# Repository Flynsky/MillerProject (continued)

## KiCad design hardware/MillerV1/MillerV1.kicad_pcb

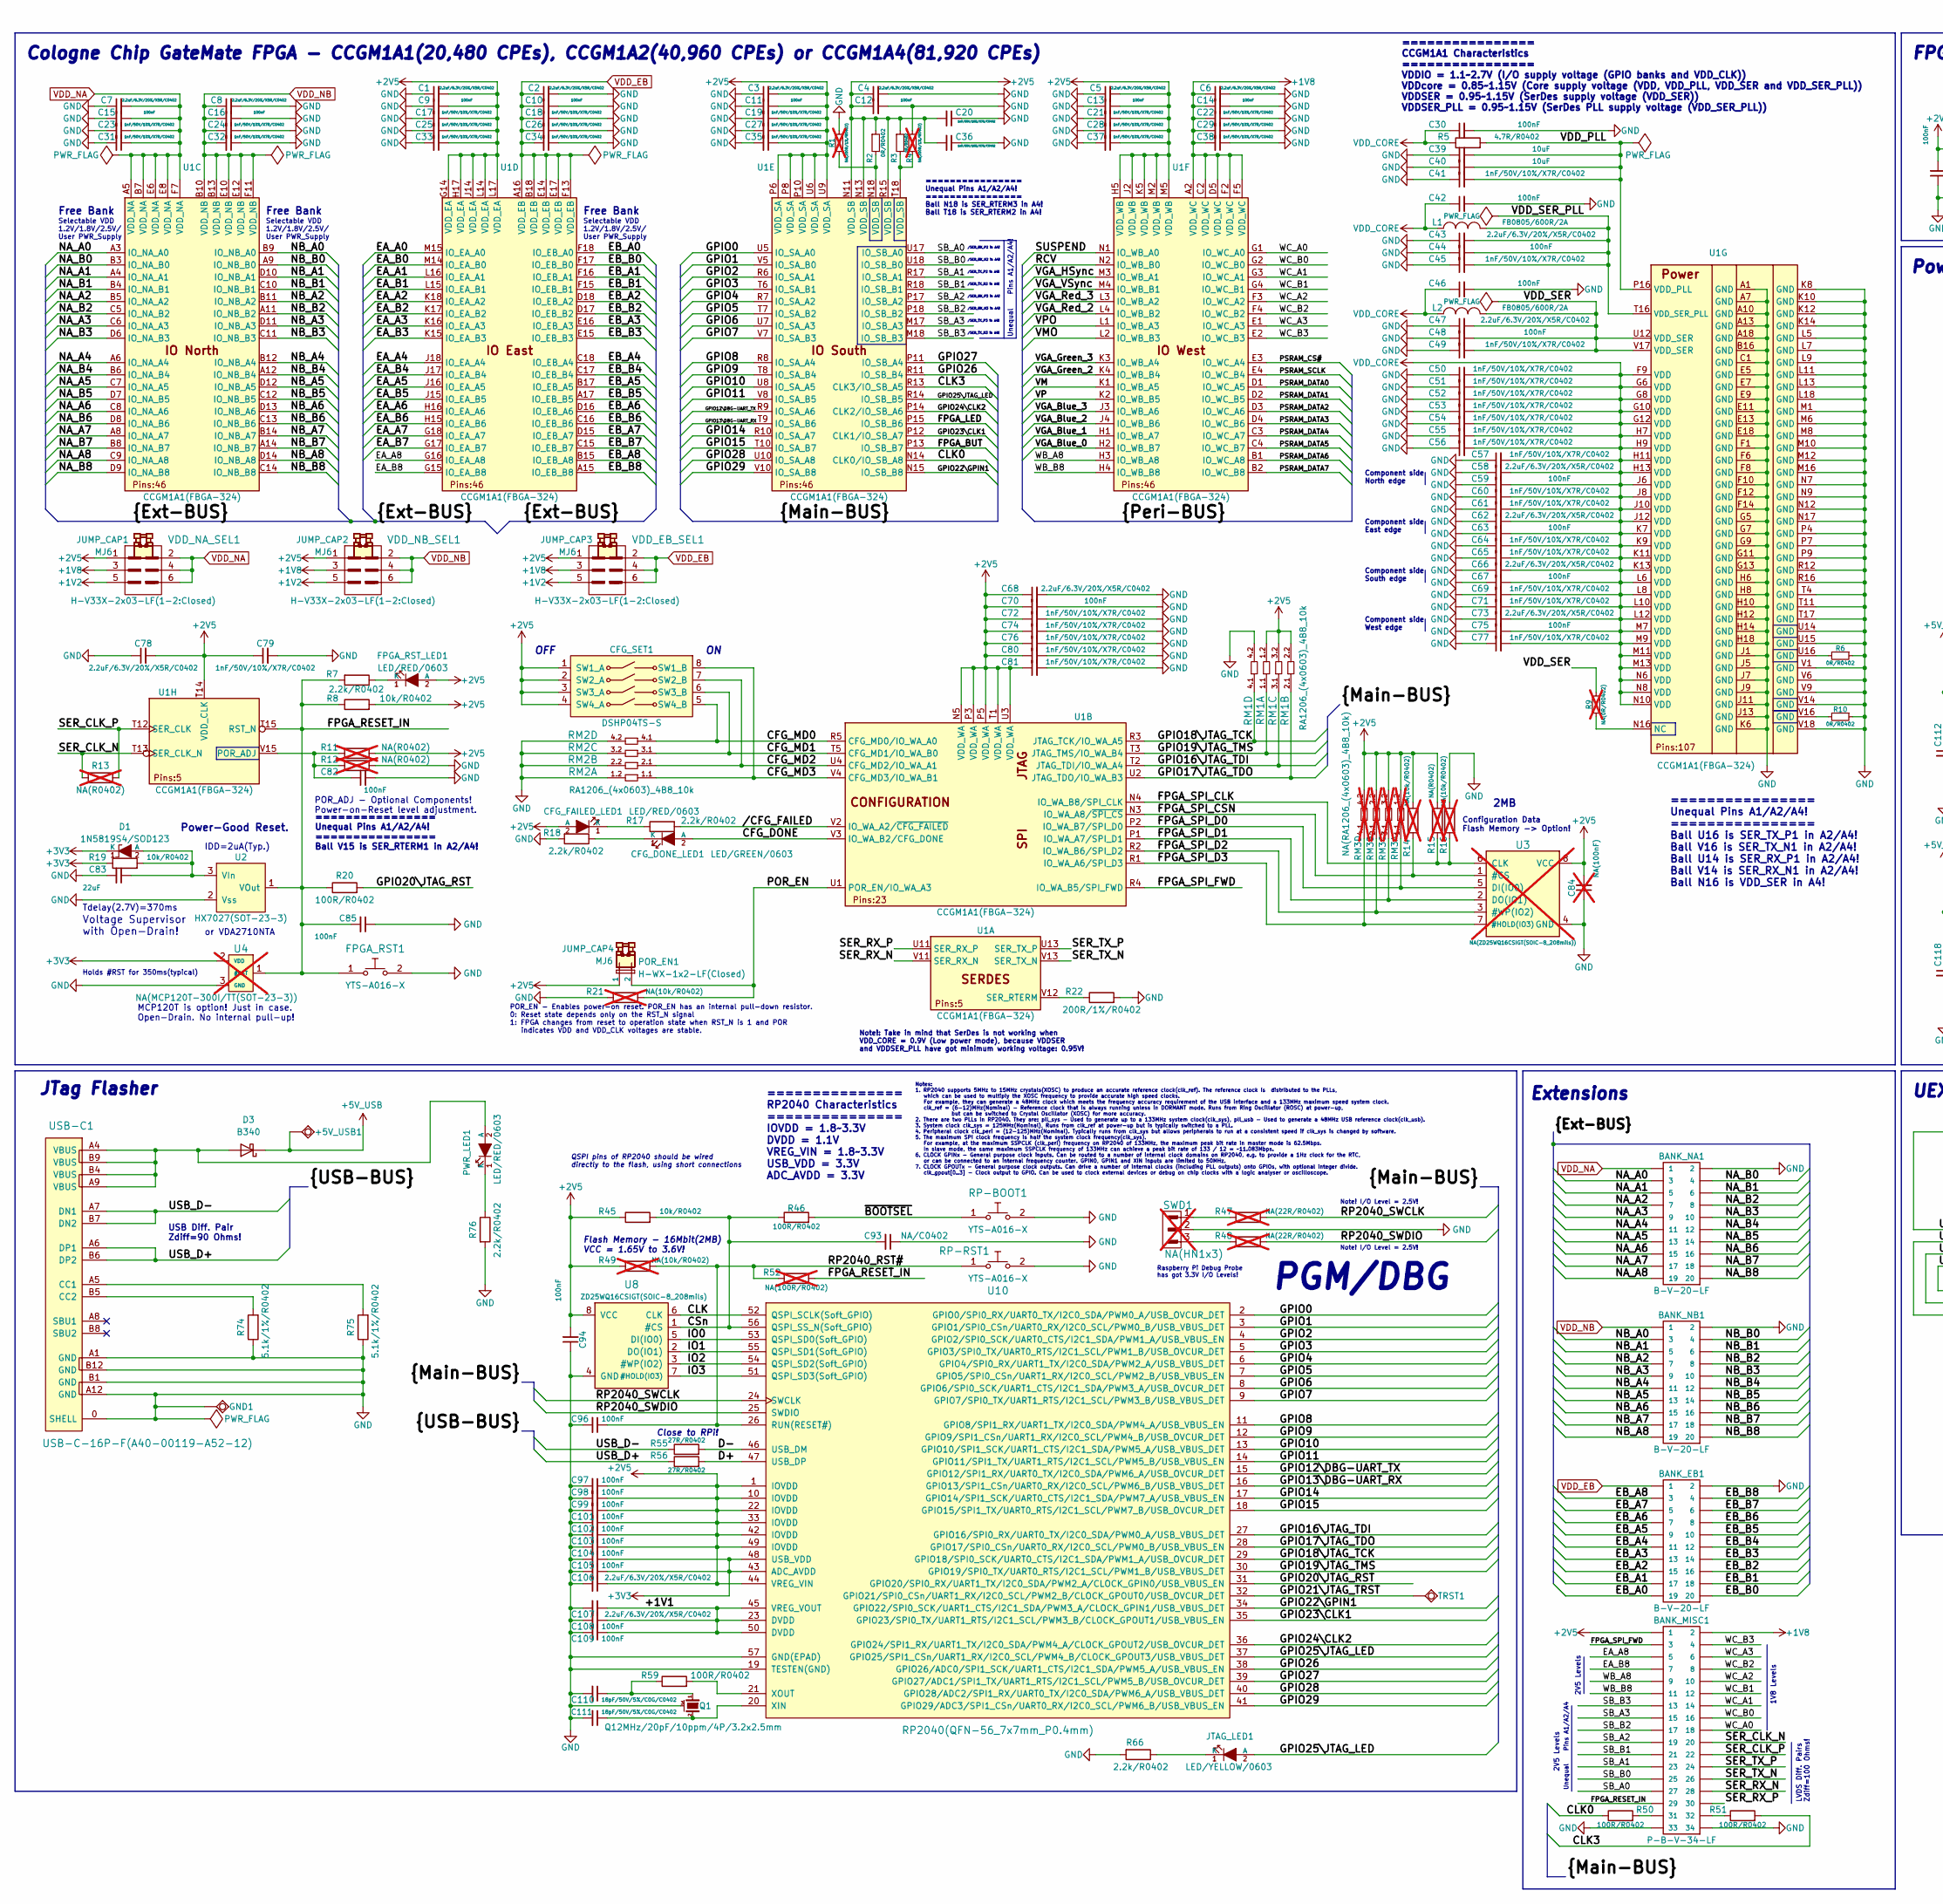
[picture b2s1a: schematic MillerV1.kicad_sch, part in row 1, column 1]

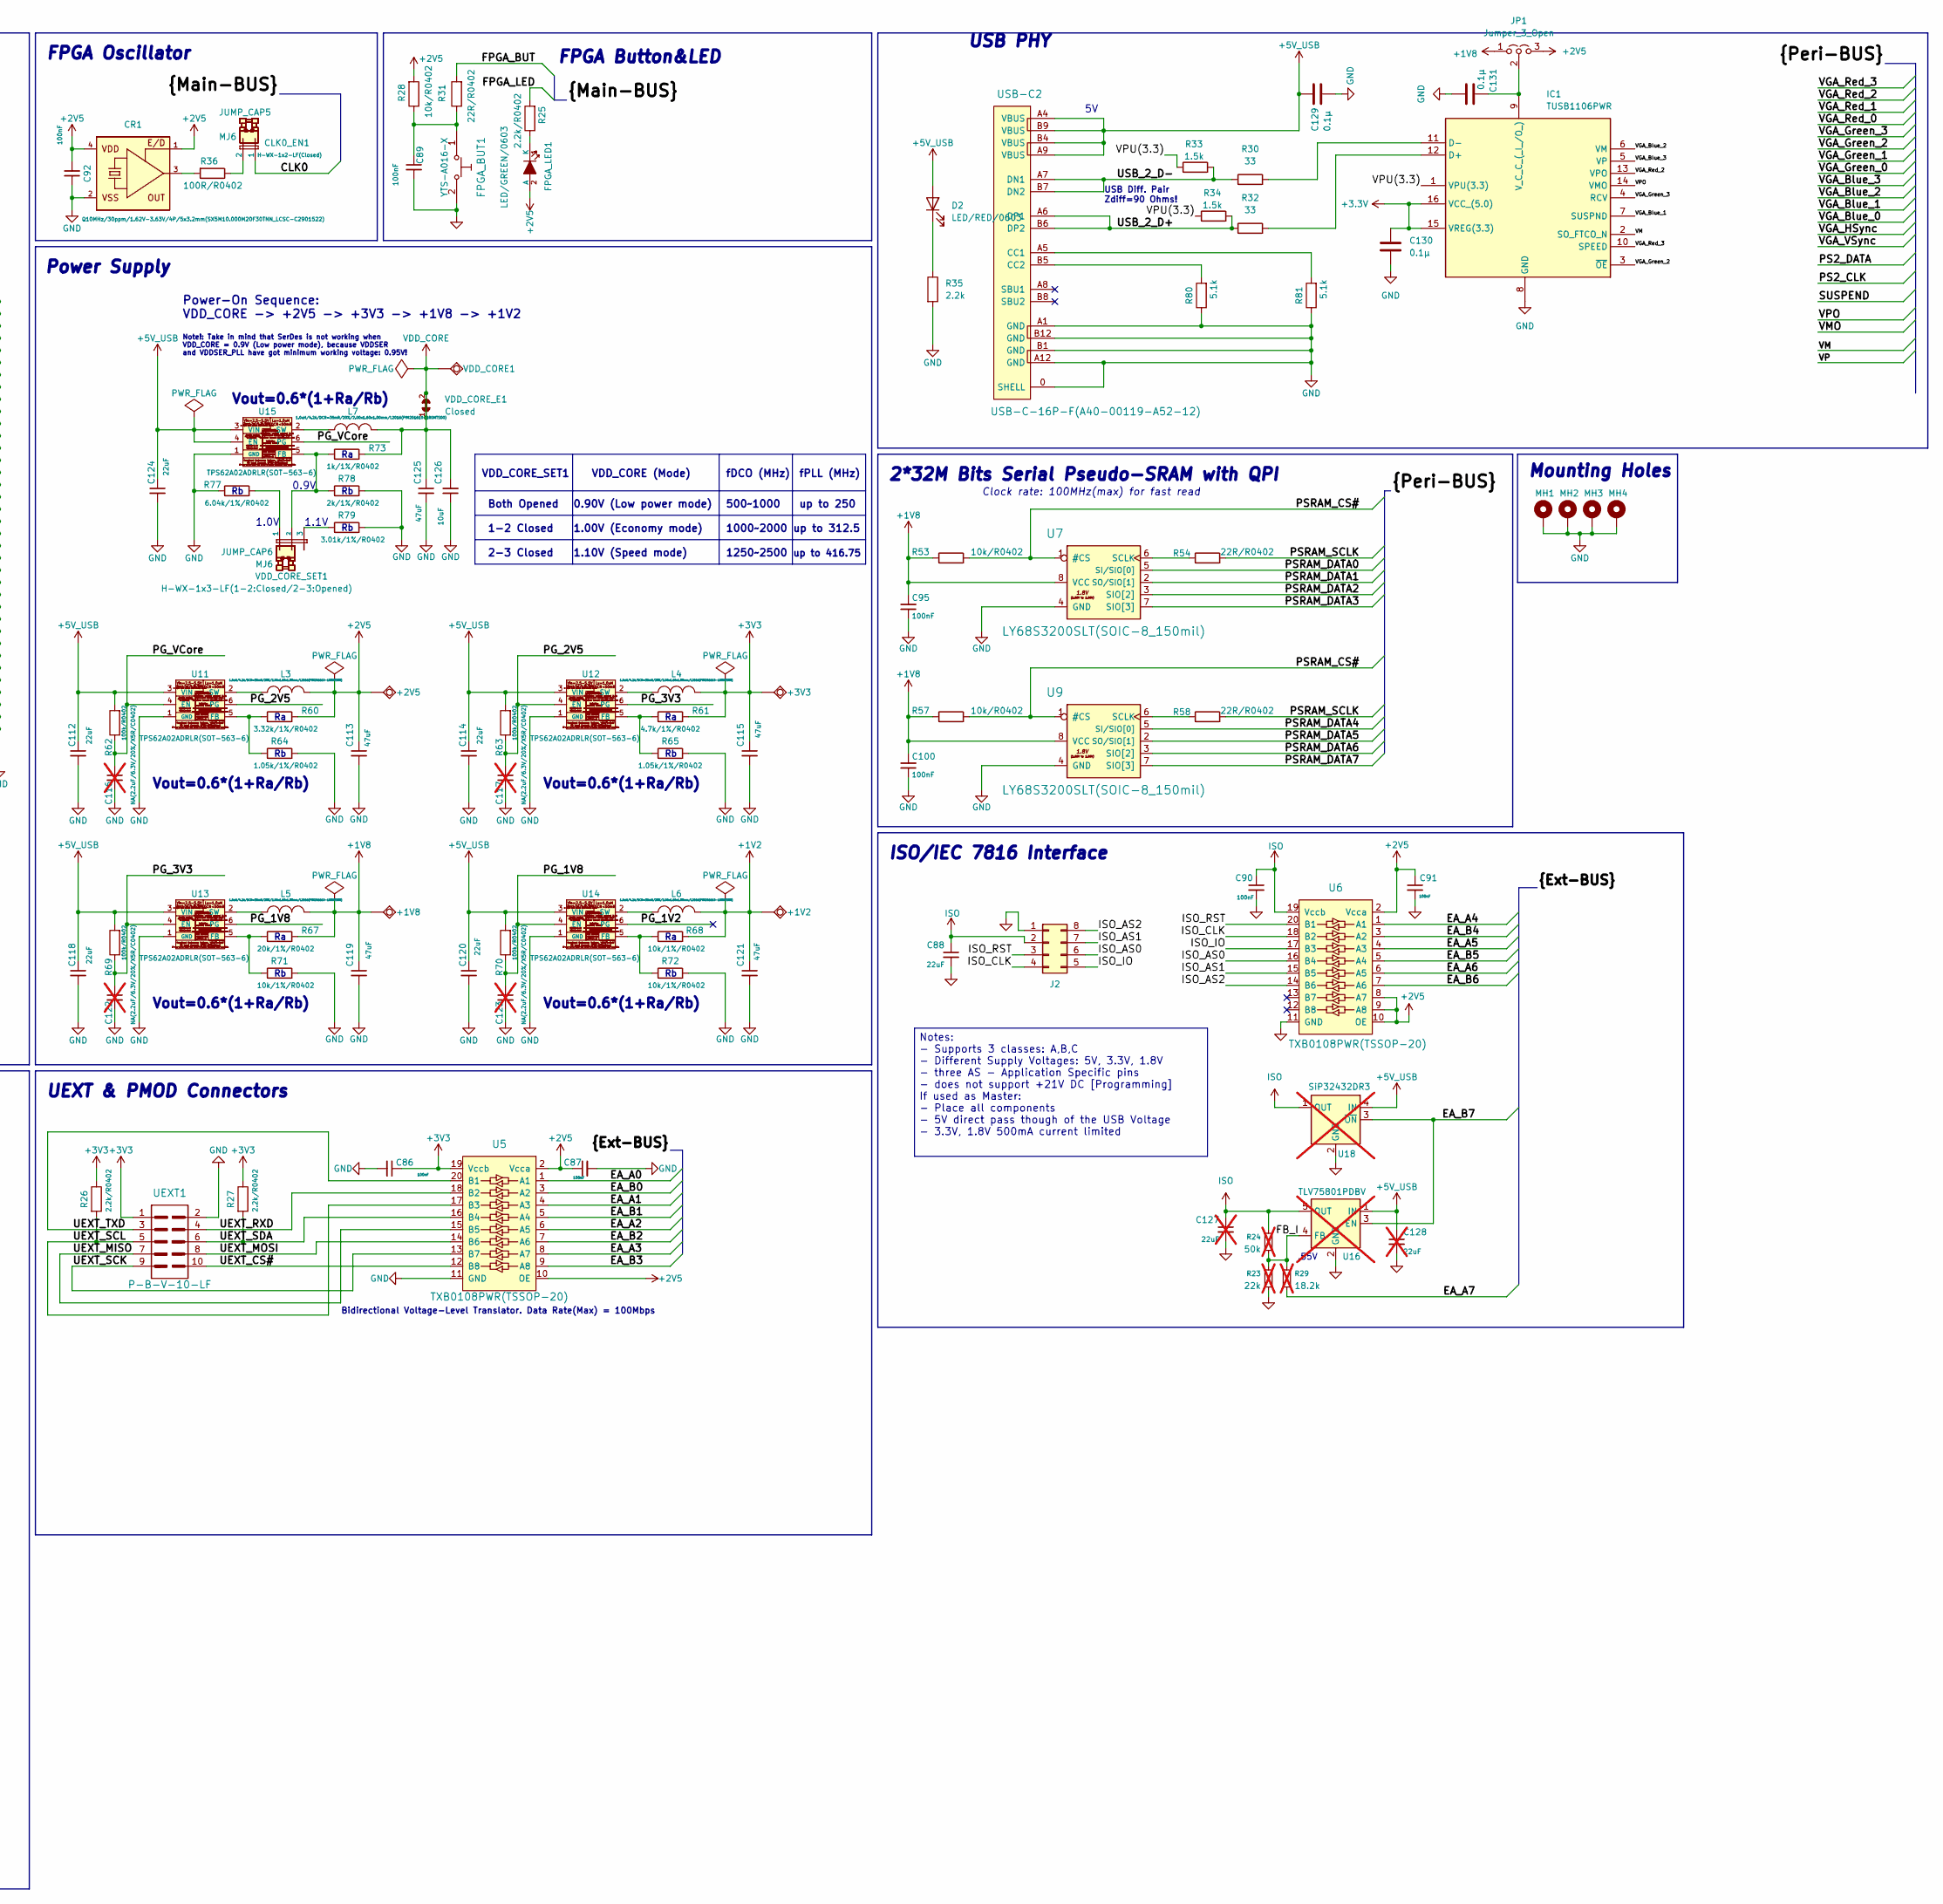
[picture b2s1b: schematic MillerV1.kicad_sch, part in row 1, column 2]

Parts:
+1V2, +1V8, +2V5, +3V3, +5V_USB1: TESTPAD; TEST_PAD_40x70_Round
BANK_EB1: B-V-20-LF; GBH-254-SMT-20
BANK_MISC1: P-B-V-34-LF; GBH-254-SMT-34
BANK_NA1: B-V-20-LF; GBH-254-SMT-20
BANK_NB1: B-V-20-LF; GBH-254-SMT-20
C1, C2, C3, C4, C5, C6, C7, C8, C43, C47, C58, C62, C66, C68, C73, C78, C106, C107: 2.2uF/6.3V/20%/X5R/C0402; C_0402_5MIL_DWS
C9, C10, C11, C12, C13, C14, C15, C16, C30, C42, C44, C46, C48, C59, C63, C67, C70, C75, C82, C85, C86, C87, C89, C90, C91, C92, C94, C95, C96, C97, C98, C99, C100, C101, C102, C103, C104, C105, C108, C109: 100nF; C_0402_5MIL_DWS
C17, C18, C19, C20, C21, C22, C23, C24, C25, C26, C27, C28, C29, C31, C32, C33, C34, C35, C36, C37, C38, C41, C45, C49, C50, C51, C52, C53, C54, C55, C56, C57, C60, C61, C64, C65, C69, C71, C72, C74, C76, C77, C79, C80, C81: 1nF/50V/10%/X7R/C0402; C_0402_5MIL_DWS
C39, C40, C126: 10uF; C_0402_5MIL_DWS
C83, C112, C114, C118, C120, C124: 22uF; C_0603_5MIL_DWS
C84: NA(100nF); C_0402_5MIL_DWS; not fitted
C88: 22uF; C_0603_1608Metric_Pad1.08x0.95mm_HandSolder
C93: NA/C0402; C_0402_5MIL_DWS
C110, C111: 18pF/50V/5%/C0G/C0402; C_0402_5MIL_DWS
C113, C115, C119, C121, C125: 47uF; C_0805_5MIL_DWS
C116, C117, C122, C123: NA(2.2uF/6.3V/20%/X5R/C0402); C_0402_5MIL_DWS; not fitted
C127, C128: 22uF; C_0603_1608Metric_Pad1.08x0.95mm_HandSolder; not fitted
C129, C130, C131: 0.1µ; C_0402_5MIL_DWS
CFG_DONE_LED1: LED/GREEN/0603; LED_0603_KA
CFG_FAILED_LED1: LED/RED/0603; LED_0603_KA
CFG_SET1: DSHP04TS-S; DSHP04TS-S-1.27mm_Half_4_Slide
CLK0_EN1: H-WX-1x2-LF(Closed); HN1x2(SMD)_H-WX-1x2-LF
CR1: Q10MHz/30ppm/1.62V-3.63V/4P/5x3.2mm(SX5M10.000M20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; 5032-4P_HCX-3S
D1: 1N5819S4/SOD123; SOD-123_1C-2A_KA
D2: LED/RED/0603; LED_0603_1608Metric
D3: B340; D_SMC
FPGA_BUT1: YTS-A016-X
FPGA_LED1: LED/GREEN/0603; LED_0603_KA
FPGA_RST1: YTS-A016-X
FPGA_RST_LED1: LED/RED/0603; LED_0603_KA
GND1: TESTPAD; TEST_PAD_40x70_Round
IC1: TUSB1106PWR; SOP65P640X120-16N; Mouser Part Number 595-TUSB1106PWR
J2: Conn_02x04_Counter_Clockwise; PinHeader_2x04_P2.54mm_Horizontal
JP1: Jumper_3_Open; SolderJumper-3_P1.3mm_Open_RoundedPad1.0x1.5mm_NumberLabels
JTAG_LED1: LED/YELLOW/0603; LED_0603_KA
JUMP_CAP1, JUMP_CAP2, JUMP_CAP3, JUMP_CAP4, JUMP_CAP5, JUMP_CAP6: MJ6
L1, L2: FB0805/600R/2A; L_0805_5MIL_DWS
L3, L4, L5, L6, L7: 1.0uH/4.2A/DCR=35mR/20%/2.00x1.60x1.00mm/L2016(PI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; L_2016_MM
MH1, MH2, MH3, MH4: MountingHole_Pad; MountingHole_3.2mm_M3_Pad_Via
POR_EN1: H-WX-1x2-LF(Closed); HN1x2(SMD)_H-WX-1x2-LF
PWR_LED1: LED/RED/0603; LED_0603_KA
Q1: Q12MHz/20pF/10ppm/4P/3.2x2.5mm; TSX-3.2x2.5mm_GND(3)
R1, R4: NA(200R/1%/R0402); R_0402_5MIL_DWS; not fitted
R2, R3, R6, R10: 0R/R0402; R_0402_5MIL_DWS
R5: 4.7R/R0402; R_0402_5MIL_DWS
R7, R17, R18, R25, R26, R27, R66, R76: 2.2k/R0402; R_0402_5MIL_DWS
R8, R19, R28, R45, R53, R57: 10k/R0402; R_0402_5MIL_DWS
R9: NA(0R/R0402); R_0402_5MIL_DWS; not fitted
R11, R12, R13, R15: NA(R0402); R_0402_5MIL_DWS; not fitted
R14, R16, R21, R49: NA(10k/R0402); R_0402_5MIL_DWS; not fitted
R20, R36, R46, R50, R51, R59: 100R/R0402; R_0402_5MIL_DWS
R22: 200R/1%/R0402; R_0402_5MIL_DWS
R23: 22k; R_0402_1005Metric_Pad0.72x0.64mm_HandSolder; not fitted
R24: 50k; R_0402_1005Metric_Pad0.72x0.64mm_HandSolder; not fitted
R29: 18.2k; R_0402_1005Metric_Pad0.72x0.64mm_HandSolder; not fitted
R30, R32: 33; R_0402_5MIL_DWS
R31, R54, R58: 22R/R0402; R_0402_5MIL_DWS
R33, R34: 1.5k; R_0402_5MIL_DWS
R35: 2.2k; R_0402_5MIL_DWS
R47, R48: NA(22R/R0402); R_0402_5MIL_DWS; not fitted
R52: NA(100R/R0402); R_0402_5MIL_DWS; not fitted
R55, R56: 27R/R0402; R_0402_5MIL_DWS
R60: 3.32k/1%/R0402; R_0402_5MIL_DWS
R61: 4.7k/1%/R0402; R_0402_5MIL_DWS
R62, R63, R69, R70: 100k/R0402; R_0402_5MIL_DWS
R64, R65: 1.05k/1%/R0402; R_0402_5MIL_DWS
R67: 20k/1%/R0402; R_0402_5MIL_DWS
R68, R71, R72: 10k/1%/R0402; R_0402_5MIL_DWS
R73: 1k/1%/R0402; R_0402_5MIL_DWS
R74, R75: 5.1k/1%/R0402; R_0402_5MIL_DWS
R77: 6.04k/1%/R0402; R_0402_5MIL_DWS
R78: 2k/1%/R0402; R_0402_5MIL_DWS
R79: 3.01k/1%/R0402; R_0402_5MIL_DWS
R80, R81: 5.1k; R_0402_1005Metric_Pad0.72x0.64mm_HandSolder
RM1, RM2: RA1206_(4x0603)_4B8_10k; RA1206_(4X0603)_4B8_xx
RM3: NA(RA1206_(4x0603)_4B8_10k); RA1206_(4X0603)_4B8_xx; not fitted
RP-BOOT1: YTS-A016-X
RP-RST1: YTS-A016-X
SWD1: NA(HN1x3); HN1x3; not fitted
TRST1: TESTPAD; TEST_PAD_40x70_Round
U1: CCGM1A1(FBGA-324); FBGA-324_P0.8mm_Pad0.4mm_Ball0.45mm_Dim15.00x15.00x1.20mm
U2: HX7027(SOT-23-3); SOT-23
U3: NA(ZD25WQ16CSIGT(SOIC-8_208mils)); SO-8_208mil; not fitted
U4: NA(MCP120T-300I/TT(SOT-23-3)); SOT-23; not fitted
U5, U6: TXB0108PWR(TSSOP-20); TSSOP20_Pitch-0.65mm_6.6x4.5x1.2mm
U7, U9: LY68S3200SLT(SOIC-8_150mil); SOIC-8_150mil
U8: ZD25WQ16CSIGT(SOIC-8_208mils); SO-8_208mil
U10: RP2040(QFN-56_7x7mm_P0.4mm); QFN56_7x7_Pitch_0.4mm
U11, U12, U13, U14, U15: TPS62A02ADRLR(SOT-563-6); SOT-563-6
U16: TLV75801PDBV; SOT-23-5; not fitted
U18: SiP32432DR3; SOT-363_SC-70-6; not fitted
UEXT1: P-B-V-10-LF; GBH-254-SMT-10
USB-C1, USB-C2: USB-C-16P-F(A40-00119-A52-12); USB2.0_TYPE-C(A40-00119-A52-12)_Paste
VDD_CORE1: TESTPAD; TEST_PAD_40x70_Round
VDD_CORE_E1: Closed; SJ_Closed
VDD_CORE_SET1: H-WX-1x3-LF(1-2:Closed/2-3:Opened); HN1x3(SMD)_H-WX-1x3-LF
VDD_EB_SEL1: H-V33X-2x03-LF(1-2:Closed); GPH254SMT02x03(H-V33X-2X3-LF)
VDD_NA_SEL1: H-V33X-2x03-LF(1-2:Closed); GPH254SMT02x03(H-V33X-2X3-LF)
VDD_NB_SEL1: H-V33X-2x03-LF(1-2:Closed); GPH254SMT02x03(H-V33X-2X3-LF)

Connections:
+1V2: +1V2.1 (Pad_1), C121.1, L6.2, R68.2, VDD_EB_SEL1.5, VDD_NA_SEL1.5, VDD_NB_SEL1.5
+1V8: +1V8.1 (Pad_1), BANK_MISC1.2, C6.1, C14.1, C22.2, C29.2, C38.2, C95.2, C100.2, C119.1, JP1.1 (A), L5.2, R53.1, R57.1, R67.2, U1.A2 (VDD_WC), U1.C2 (VDD_WC), U1.D5 (VDD_WC), U1.F2 (VDD_WC), U1.F5 (VDD_WC), U7.8 (VCC), U9.8 (VCC), VDD_EB_SEL1.3, VDD_NA_SEL1.3, VDD_NB_SEL1.3
+2V5: +2V5.1 (Pad_1), BANK_MISC1.1, C1.2, C3.2, C4.1, C5.2, C9.1, C11.1, C12.1, C13.1, C17.1, C19.1, C20.2, C21.1, C25.1, C27.1, C28.1, C33.1, C35.1, C36.2, C37.1, C68.1, C70.1, C72.1, C74.1, C76.1, C78.2, C79.1, C80.1, C81.1, C84.2, C87.1, C91.1, C92.2, C94.2, C97.1, C98.1, C99.1, C101.1, C102.1, C103.1, C106.1, C113.1, CFG_FAILED_LED1.2 (A), CFG_SET1.1 (SW1_A), CFG_SET1.2 (SW2_A), CFG_SET1.3 (SW3_A), CFG_SET1.4 (SW4_A), CR1.1 (E/D), CR1.4 (VDD), FPGA_LED1.2 (A), FPGA_RST_LED1.2 (A), JP1.3 (B), L3.2, POR_EN1.1, R2.1, R3.1, R8.2, R11.2, R14.2, R15.2, R28.2, R45.1, R49.1, R60.2, RM1.1.2, RM1.2.2, RM1.3.2, RM3.1.2, RM3.2.2, RM3.3.2, RM3.4.2, U1.G14 (VDD_EA), U1.H5 (VDD_WB), U1.H17 (VDD_EA), U1.J2 (VDD_WB), U1.J14 (VDD_EA), U1.K5 (VDD_WB), U1.L14 (VDD_EA), U1.L17 (VDD_EA), U1.M2 (VDD_WB), U1.M5 (VDD_WB), U1.N5 (VDD_WA), U1.N11 (VDD_SB), U1.N13 (VDD_SB), U1.P3 (VDD_WA), U1.P5 (VDD_WA)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
+3.3V: C130.1, IC1.15 (VREG(3.3)), IC1.16 (VCC_(5.0))
+3V3: +3V3.1 (Pad_1), C86.1, C104.1, C105.1, C115.1, D1.1 (K), L4.2, R19.1, R26.1, R27.1, R61.2, U4.2 (VDD), U5.19 (Vccb), U10.43 (ADC_AVDD), U10.48 (USB_VDD), UEXT1.1
+5V_USB: +5V_USB1.1 (Pad_1), C112.1, C114.1, C118.1, C120.1, C124.1, C128.1, C129.1, D2.2 (A), D3.1 (K), R62.2, R63.2, R69.2, R70.2, U11.3 (VIN), U12.3 (VIN), U13.3 (VIN), U14.3 (VIN), U15.3 (VIN), U15.4 (EN), U16.1 (IN), U18.4 (IN), USB-C2.A4 (VBUS), USB-C2.A9 (VBUS), USB-C2.B4 (VBUS), USB-C2.B9 (VBUS)
/+1V1: C107.1, C108.1, C109.1, U10.23 (DVDD), U10.45 (VREG_VOUT), U10.50 (DVDD)
/CFG_DONE: CFG_DONE_LED1.2 (A), U1.V3 (IO_WA_B2/CFG_DONE)
/CFG_MD0: CFG_SET1.5 (SW4_B), RM2.4.1, U1.R5 (CFG_MD0/IO_WA_A0)
/CFG_MD1: CFG_SET1.6 (SW3_B), RM2.3.1, U1.T5 (CFG_MD1/IO_WA_B0)
/CFG_MD2: CFG_SET1.7 (SW2_B), RM2.2.1, U1.U4 (CFG_MD2/IO_WA_A1)
/CFG_MD3: CFG_SET1.8 (SW1_B), RM2.1.1, U1.V4 (CFG_MD3/IO_WA_B1)
/CLK: U8.6 (CLK), U10.52 (QSPI_SCLK(Soft_GPIO))
/CLK0: CLK0_EN1.1, R50.1, U1.N14 (CLK0/IO_SB_A8)
/CLK3: R51.2, U1.R13 (CLK3/IO_SB_A5)
/CSn: C93.2, R45.2, R46.1, U8.1 (#CS), U10.56 (QSPI_SS_N(Soft_GPIO))
/D+: R56.2, U10.47 (USB_DP)
/D-: R55.2, U10.46 (USB_DM)
/EA_A0: U1.M15 (IO_EA_A0), U5.1 (A1)
/EA_A1: U1.L16 (IO_EA_A1), U5.4 (A3)
/EA_A2: U1.K18 (IO_EA_A2), U5.6 (A5)
/EA_A3: U1.K16 (IO_EA_A3), U5.8 (A7)
/EA_A4: U1.J18 (IO_EA_A4), U6.1 (A1)
/EA_A5: U1.J16 (IO_EA_A5), U6.4 (A3)
/EA_A6: U1.H16 (IO_EA_A6), U6.6 (A5)
/EA_A7: R29.2, U1.G18 (IO_EA_A7)
/EA_A8: BANK_MISC1.5, U1.G16 (IO_EA_A8)
/EA_B0: U1.M14 (IO_EA_B0), U5.3 (A2)
/EA_B1: U1.L15 (IO_EA_B1), U5.5 (A4)
/EA_B2: U1.K17 (IO_EA_B2), U5.7 (A6)
/EA_B3: U1.K15 (IO_EA_B3), U5.9 (A8)
/EA_B4: U1.J17 (IO_EA_B4), U6.3 (A2)
/EA_B5: U1.J15 (IO_EA_B5), U6.5 (A4)
/EA_B6: U1.H15 (IO_EA_B6), U6.7 (A6)
/EA_B7: U1.G17 (IO_EA_B7), U16.3 (EN), U18.3 (~ON)
/EA_B8: BANK_MISC1.7, U1.G15 (IO_EA_B8)
/EB_A0: BANK_EB1.19, U1.F18 (IO_EB_A0)
/EB_A1: BANK_EB1.17, U1.F16 (IO_EB_A1)
/EB_A2: BANK_EB1.15, U1.D18 (IO_EB_A2)
/EB_A3: BANK_EB1.13, U1.E16 (IO_EB_A3)
/EB_A4: BANK_EB1.11, U1.C18 (IO_EB_A4)
/EB_A5: BANK_EB1.9, U1.B17 (IO_EB_A5)
/EB_A6: BANK_EB1.7, U1.D16 (IO_EB_A6)
/EB_A7: BANK_EB1.5, U1.D15 (IO_EB_A7)
/EB_A8: BANK_EB1.3, U1.B15 (IO_EB_A8)
/EB_B0: BANK_EB1.20, U1.F17 (IO_EB_B0)
/EB_B1: BANK_EB1.18, U1.F15 (IO_EB_B1)
/EB_B2: BANK_EB1.16, U1.D17 (IO_EB_B2)
/EB_B3: BANK_EB1.14, U1.E15 (IO_EB_B3)
/EB_B4: BANK_EB1.12, U1.C17 (IO_EB_B4)
/EB_B5: BANK_EB1.10, U1.A17 (IO_EB_B5)
/EB_B6: BANK_EB1.8, U1.C16 (IO_EB_B6)
/EB_B7: BANK_EB1.6, U1.C15 (IO_EB_B7)
/EB_B8: BANK_EB1.4, U1.A15 (IO_EB_B8)
/FB_I: R23.1, R24.2, R29.1, U16.4 (FB)
/FPGA_BUT: R31.2, U1.P13 (IO_SB_B7)
/FPGA_LED: R25.2, U1.P15 (IO_SB_B6)
/FPGA_RESET_IN: BANK_MISC1.29, C85.2, FPGA_RST1.1, R7.2, R8.1, R20.1, R52.2, U1.T15 (RST_N), U2.1 (VOut), U4.1 (#RST)
/FPGA_SPI_CLK: R15.1, R16.1, U1.N4 (IO_WA_B8/SPI_CLK), U3.6 (CLK)
/FPGA_SPI_CSN: R14.1, U1.N3 (IO_WA_A8/~SPI_CS), U3.1 (#CS)
/FPGA_SPI_D0: RM3.1.1, U1.P2 (IO_WA_B7/SPI_D0), U3.5 (DI(IO0))
/FPGA_SPI_D1: RM3.3.1, U1.P1 (IO_WA_A7/SPI_D1), U3.2 (DO(IO1))
/FPGA_SPI_D2: RM3.2.1, U1.R2 (IO_WA_B6/SPI_D2), U3.3 (#WP(IO2))
/FPGA_SPI_D3: RM3.4.1, U1.R1 (IO_WA_A6/SPI_D3), U3.7 (#HOLD(IO3))
/FPGA_SPI_FWD: BANK_MISC1.3, U1.R4 (IO_WA_B5/SPI_FWD)
/GPIO0: U1.U5 (IO_SA_A0), U10.2 (GPIO0/SPI0_RX/UART0_TX/I2C0_SDA/PWM0_A/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)
/GPIO1: U1.V5 (IO_SA_B0), U10.3 (GPIO1/SPI0_CSn/UART0_RX/I2C0_SCL/PWM0_B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)
/GPIO2: U1.R6 (IO_SA_A1), U10.4 (GPIO2/SPI0_SCK/UART0_CTS/I2C1_SDA/PWM1_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)
/GPIO3: U1.T6 (IO_SA_B1), U10.5 (GPIO3/SPI0_TX/UART0_RTS/I2C1_SCL/PWM1_B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)
/GPIO4: U1.R7 (IO_SA_A2), U10.6 (GPIO4/SPI0_RX/UART1_TX/I2C0_SDA/PWM2_A/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)
/GPIO5: U1.T7 (IO_SA_B2), U10.7 (GPIO5/SPI0_CSn/UART1_RX/I2C0_SCL/PWM2_B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)
/GPIO6: U1.U7 (IO_SA_A3), U10.8 (GPIO6/SPI0_SCK/UART1_CTS/I2C1_SDA/PWM3_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)
/GPIO7: U1.V7 (IO_SA_B3), U10.9 (GPIO7/SPI0_TX/UART1_RTS/I2C1_SCL/PWM3_B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)
/GPIO8: U1.R8 (IO_SA_A4), U10.11 (GPIO8/SPI1_RX/UART1_TX/I2C0_SDA/PWM4_A/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)
/GPIO9: U1.T8 (IO_SA_B4), U10.12 (GPIO9/SPI1_CSn/UART1_RX/I2C0_SCL/PWM4_B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)
/GPIO10: U1.U8 (IO_SA_A5), U10.13 (GPIO10/SPI1_SCK/UART1_CTS/I2C1_SDA/PWM5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)
/GPIO11: U1.V8 (IO_SA_B5), U10.14 (GPIO11/SPI1_TX/UART1_RTS/I2C1_SCL/PWM5_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)
/GPIO12\DBG-UART_TX: U1.R9 (IO_SA_A6), U10.15 (GPIO12/SPI1_RX/UART0_TX/I2C0_SDA/PWM6_A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)
/GPIO13\DBG-UART_RX: U1.T9 (IO_SA_B6), U10.16 (GPIO13/SPI1_CSn/UART0_RX/I2C0_SCL/PWM6_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)
/GPIO14: U1.R10 (IO_SA_A7), U10.17 (GPIO14/SPI1_SCK/UART0_CTS/I2C1_SDA/PWM7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)
/GPIO15: U1.T10 (IO_SA_B7), U10.18 (GPIO15/SPI1_TX/UART0_RTS/I2C1_SCL/PWM7_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)
/GPIO16\JTAG_TDI: RM1.3.1, U1.T2 (JTAG_TDI/IO_WA_A4), U10.27 (GPIO16/SPI0_RX/UART0_TX/I2C0_SDA/PWM0_A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)
/GPIO17\JTAG_TDO: RM1.2.1, U1.U2 (JTAG_TDO/IO_WA_B3), U10.28 (GPIO17/SPI0_CSn/UART0_RX/I2C0_SCL/PWM0_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)
/GPIO18\JTAG_TCK: RM1.4.1, U1.R3 (JTAG_TCK/IO_WA_A5), U10.29 (GPIO18/SPI0_SCK/UART0_CTS/I2C1_SDA/PWM1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)
/GPIO19\JTAG_TMS: RM1.1.1, U1.T3 (JTAG_TMS/IO_WA_B4), U10.30 (GPIO19/SPI0_TX/UART0_RTS/I2C1_SCL/PWM1_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)
/GPIO20\JTAG_RST: R20.2, U10.31 (GPIO20/SPI0_RX/UART1_TX/I2C0_SDA/PWM2_A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)
/GPIO21\JTAG_TRST: TRST1.1 (Pad_1), U10.32 (GPIO21/SPI0_CSn/UART1_RX/I2C0_SCL/PWM2_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)
/GPIO22\GPIN1: U1.N15 (IO_SB_B8), U10.34 (GPIO22/SPI0_SCK/UART1_CTS/I2C1_SDA/PWM3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)
/GPIO23\CLK1: U1.P12 (CLK1/IO_SB_A7), U10.35 (GPIO23/SPI0_TX/UART1_RTS/I2C1_SCL/PWM3_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)
/GPIO24\CLK2: U1.P14 (CLK2/IO_SB_A6), U10.36 (GPIO24/SPI1_RX/UART1_TX/I2C0_SDA/PWM4_A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)
/GPIO25\JTAG_LED: JTAG_LED1.2 (A), U1.R14 (IO_SB_B5), U10.37 (GPIO25/SPI1_CSn/UART1_RX/I2C0_SCL/PWM4_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)
/GPIO26: U1.R11 (IO_SB_B4), U10.38 (GPIO26/ADC0/SPI1_SCK/UART1_CTS/I2C1_SDA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)
/GPIO27: U1.P11 (IO_SB_A4), U10.39 (GPIO27/ADC1/SPI1_TX/UART1_RTS/I2C1_SCL/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)
/GPIO28: U1.U10 (IO_SA_A8), U10.40 (GPIO28/ADC2/SPI1_RX/UART0_TX/I2C0_SDA/P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)
/GPIO29: U1.V10 (IO_SA_B8), U10.41 (GPIO29/ADC3/SPI1_CSn/UART0_RX/I2C0_SCL/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)
/IO0: U8.5 (DI(IO0)), U10.53 (QSPI_SD0(Soft_GPIO))
/IO1: U8.2 (DO(IO1)), U10.55 (QSPI_SD1(Soft_GPIO))
/IO2: U8.3 (#WP(IO2)), U10.54 (QSPI_SD2(Soft_GPIO))
/IO3: U8.7 (#HOLD(IO3)), U10.51 (QSPI_SD3(Soft_GPIO))
/ISO_AS0: J2.6, U6.16 (B4)
/ISO_AS1: J2.7, U6.15 (B5)
/ISO_AS2: J2.8, U6.14 (B6)
/ISO_CLK: J2.4, U6.18 (B2)
/ISO_IO: J2.5, U6.17 (B3)
/ISO_RST: J2.3, U6.20 (B1)
/NA_A0: BANK_NA1.3, U1.A3 (IO_NA_A0)
/NA_A1: BANK_NA1.5, U1.A4 (IO_NA_A1)
/NA_A2: BANK_NA1.7, U1.B5 (IO_NA_A2)
/NA_A3: BANK_NA1.9, U1.C6 (IO_NA_A3)
/NA_A4: BANK_NA1.11, U1.A6 (IO_NA_A4)
/NA_A5: BANK_NA1.13, U1.C7 (IO_NA_A5)
/NA_A6: BANK_NA1.15, U1.C8 (IO_NA_A6)
/NA_A7: BANK_NA1.17, U1.A8 (IO_NA_A7)
/NA_A8: BANK_NA1.19, U1.C9 (IO_NA_A8)
/NA_B0: BANK_NA1.4, U1.B3 (IO_NA_B0)
/NA_B1: BANK_NA1.6, U1.B4 (IO_NA_B1)
/NA_B2: BANK_NA1.8, U1.C5 (IO_NA_B2)
/NA_B3: BANK_NA1.10, U1.D6 (IO_NA_B3)
/NA_B4: BANK_NA1.12, U1.B6 (IO_NA_B4)
/NA_B5: BANK_NA1.14, U1.D7 (IO_NA_B5)
/NA_B6: BANK_NA1.16, U1.D8 (IO_NA_B6)
/NA_B7: BANK_NA1.18, U1.B8 (IO_NA_B7)
/NA_B8: BANK_NA1.20, U1.D9 (IO_NA_B8)
/NB_A0: BANK_NB1.3, U1.B9 (IO_NB_A0)
/NB_A1: BANK_NB1.5, U1.D10 (IO_NB_A1)
/NB_A2: BANK_NB1.7, U1.B11 (IO_NB_A2)
/NB_A3: BANK_NB1.9, U1.D11 (IO_NB_A3)
/NB_A4: BANK_NB1.11, U1.B12 (IO_NB_A4)
/NB_A5: BANK_NB1.13, U1.D12 (IO_NB_A5)
/NB_A6: BANK_NB1.15, U1.D13 (IO_NB_A6)
/NB_A7: BANK_NB1.17, U1.B14 (IO_NB_A7)
/NB_A8: BANK_NB1.19, U1.D14 (IO_NB_A8)
/NB_B0: BANK_NB1.4, U1.A9 (IO_NB_B0)
/NB_B1: BANK_NB1.6, U1.C10 (IO_NB_B1)
/NB_B2: BANK_NB1.8, U1.A11 (IO_NB_B2)
/NB_B3: BANK_NB1.10, U1.C11 (IO_NB_B3)
/NB_B4: BANK_NB1.12, U1.A12 (IO_NB_B4)
/NB_B5: BANK_NB1.14, U1.C12 (IO_NB_B5)
/NB_B6: BANK_NB1.16, U1.C13 (IO_NB_B6)
/NB_B7: BANK_NB1.18, U1.A14 (IO_NB_B7)
/NB_B8: BANK_NB1.20, U1.C14 (IO_NB_B8)
/PG_1V2: U14.6 (PG)
/PG_1V8: C123.1, R70.1, U13.6 (PG), U14.4 (EN)
/PG_2V5: C117.1, R63.1, U11.6 (PG), U12.4 (EN)
/PG_3V3: C122.1, R69.1, U12.6 (PG), U13.4 (EN)
/PG_VCore: C116.1, R62.1, U11.4 (EN), U15.6 (PG)
/POR_EN: POR_EN1.2, R21.2, U1.U1 (POR_EN/IO_WA_A3)
/PSRAM_CS#: R53.2, R57.2, U1.E3 (IO_WC_A4), U7.1 (#CS), U9.1 (#CS)
/PSRAM_DATA0: U1.D1 (IO_WC_A5), U7.5 (SI/SIO[0])
/PSRAM_DATA1: U1.D2 (IO_WC_B5), U7.2 (SO/SIO[1])
/PSRAM_DATA2: U1.D3 (IO_WC_A6), U7.3 (SIO[2])
/PSRAM_DATA3: U1.D4 (IO_WC_B6), U7.7 (SIO[3])
/PSRAM_DATA4: U1.C3 (IO_WC_A7), U9.5 (SI/SIO[0])
/PSRAM_DATA5: U1.C4 (IO_WC_B7), U9.2 (SO/SIO[1])
/PSRAM_DATA6: U1.B1 (IO_WC_A8), U9.3 (SIO[2])
/PSRAM_DATA7: U1.B2 (IO_WC_B8), U9.7 (SIO[3])
/PSRAM_SCLK: R54.2, R58.2, U1.E4 (IO_WC_B4)
/RCV: U1.N2 (IO_WB_B0)
/RP2040_RST#: C96.1, R49.2, R52.1, RP-RST1.1, U10.26 (RUN(RESET#))
/RP2040_SWCLK: R47.1, U10.24 (SWCLK)
/RP2040_SWDIO: R48.1, U10.25 (SWDIO)
/SB_A0: BANK_MISC1.27, U1.U17 (IO_SB_A0)
/SB_A1: BANK_MISC1.23, U1.R17 (IO_SB_A1)
/SB_A2: BANK_MISC1.19, U1.P17 (IO_SB_A2)
/SB_A3: BANK_MISC1.15, U1.M17 (IO_SB_A3)
/SB_B0: BANK_MISC1.25, U1.U18 (IO_SB_B0)
/SB_B1: BANK_MISC1.21, U1.R18 (IO_SB_B1)
/SB_B2: BANK_MISC1.17, U1.P18 (IO_SB_B2)
/SB_B3: BANK_MISC1.13, U1.M18 (IO_SB_B3)
/SER_CLK_N: BANK_MISC1.20, R13.1, U1.T13 (SER_CLK_N)
/SER_CLK_P: BANK_MISC1.22, R13.2, U1.T12 (SER_CLK)
/SER_RX_N: BANK_MISC1.28, U1.V11 (SER_RX_N)
/SER_RX_P: BANK_MISC1.30, U1.U11 (SER_RX_P)
/SER_TX_N: BANK_MISC1.26, U1.V13 (SER_TX_N)
/SER_TX_P: BANK_MISC1.24, U1.U13 (SER_TX_P)
/SUSPEND: U1.N1 (IO_WB_A0)
/UEXT_CS#: U5.12 (B8), UEXT1.10
/UEXT_MISO: U5.15 (B5), UEXT1.7
/UEXT_MOSI: U5.14 (B6), UEXT1.8
/UEXT_RXD: U5.18 (B2), UEXT1.4
/UEXT_SCK: U5.13 (B7), UEXT1.9
/UEXT_SCL: R26.2, U5.17 (B3), UEXT1.5
/UEXT_SDA: R27.2, U5.16 (B4), UEXT1.6
/UEXT_TXD: U5.20 (B1), UEXT1.3
/USB_2_D+: R32.1, R34.2, USB-C2.A6 (DP1), USB-C2.B6 (DP2)
/USB_2_D-: R30.1, R33.2, USB-C2.A7 (DN1), USB-C2.B7 (DN2)
/USB_D+: R56.1, USB-C1.A6 (DP1), USB-C1.B6 (DP2)
/USB_D-: R55.1, USB-C1.A7 (DN1), USB-C1.B7 (DN2)
/VDD_PLL: C39.2, C40.2, C41.2, R5.2, U1.P16 (VDD_PLL)
/VDD_SER: C47.2, C48.2, C49.2, L2.2, R9.1, U1.U12 (VDD_SER), U1.V17 (VDD_SER)
/VDD_SER_PLL: C43.2, C44.2, C45.2, L1.2, U1.T16 (VDD_SER_PLL)
/VGA_Blue_0: U1.H2 (IO_WB_B7)
/VGA_Blue_1: IC1.7 (SUSPND), U1.H1 (IO_WB_A7)
/VGA_Blue_2: IC1.6 (VM), U1.J4 (IO_WB_B6)
/VGA_Blue_3: IC1.5 (VP), U1.J3 (IO_WB_A6)
/VGA_Green_2: IC1.3 (~OE), U1.K4 (IO_WB_B4)
/VGA_Green_3: IC1.4 (RCV), U1.K3 (IO_WB_A4)
/VGA_HSync: U1.M3 (IO_WB_A1)
/VGA_Red_2: IC1.13 (VPO), U1.L4 (IO_WB_B2)
/VGA_Red_3: IC1.10 (SPEED), U1.L3 (IO_WB_A2)
/VGA_VSync: U1.M4 (IO_WB_B1)
/VM: IC1.2 (SO_FTCO_N), U1.K1 (IO_WB_A5)
/VMO: U1.L2 (IO_WB_B3)
/VP: U1.K2 (IO_WB_B5)
/VPO: IC1.14 (VMO), U1.L1 (IO_WB_A3)
/VPU(3.3): IC1.1 (VPU(3.3)), R33.1, R34.1
/WB_A8: BANK_MISC1.9, U1.H3 (IO_WB_A8)
/WB_B8: BANK_MISC1.11, U1.H4 (IO_WB_B8)
/WC_A0: BANK_MISC1.18, U1.G1 (IO_WC_A0)
/WC_A1: BANK_MISC1.14, U1.G3 (IO_WC_A1)
/WC_A2: BANK_MISC1.10, U1.F3 (IO_WC_A2)
/WC_A3: BANK_MISC1.6, U1.E1 (IO_WC_A3)
/WC_B0: BANK_MISC1.16, U1.G2 (IO_WC_B0)
/WC_B1: BANK_MISC1.12, U1.G4 (IO_WC_B1)
/WC_B2: BANK_MISC1.8, U1.F4 (IO_WC_B2)
/WC_B3: BANK_MISC1.4, U1.E2 (IO_WC_B3)
//CFG_FAILED: R17.2, U1.V2 (IO_WA_A2/~CFG_FAILED)
/~BOOTSEL: R46.2, RP-BOOT1.1
GND: BANK_EB1.2, BANK_MISC1.33, BANK_MISC1.34, BANK_NA1.2, BANK_NB1.2, C1.1, C2.2, C3.1, C4.2, C5.1, C6.2, C7.1, C8.2, C9.2, C10.2, C11.2, C12.2, C13.2, C14.2, C15.2, C16.1, C17.2, C18.1, C19.2, C20.1, C21.2, C22.1, C23.2, C24.1, C25.2, C26.1, C27.2, C28.2, C29.1, C30.2, C31.2, C32.1, C33.2, C34.1, C35.2, C36.1, C37.2, C38.1, C39.1, C40.1, C41.1, C42.2, C43.1, C44.1, C45.1, C46.2, C47.1, C48.1, C49.1, C50.1, C51.1, C52.1, C53.1, C54.1, C55.1, C56.1, C57.1, C58.1, C59.1, C60.1, C61.1, C62.1, C63.1, C64.1, C65.1, C66.1, C67.1, C68.2, C69.1, C70.2, C71.1, C72.2, C73.1, C74.2, C75.1, C76.2, C77.1, C78.1, C79.2, C80.2, C81.2, C82.2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
ISO: C88.1, C90.1, C127.1, J2.2, R24.1, U6.19 (Vccb), U16.5 (OUT), U18.1 (OUT)
unnamed: BANK_MISC1.31, R50.2
unnamed: BANK_MISC1.32, R51.1
unnamed: C89.1, FPGA_BUT1.1, R28.1, R31.1
unnamed: C110.1, Q1.1, R59.1
unnamed: CFG_DONE_LED1.1 (K), R18.1
unnamed: CFG_FAILED_LED1.1 (K), R17.1
unnamed: CLK0_EN1.2, R36.1
unnamed: CR1.3 (OUT), R36.2
unnamed: C83.1, D1.2 (A), R19.2, U2.3 (VIn)
unnamed: D2.1 (K), R35.1
unnamed: D3.2 (A), PWR_LED1.2 (A), USB-C1.A4 (VBUS), USB-C1.A9 (VBUS), USB-C1.B4 (VBUS), USB-C1.B9 (VBUS)
unnamed: FPGA_LED1.1 (K), R25.1
unnamed: FPGA_RST_LED1.1 (K), R7.1
unnamed: IC1.12 (D+), R32.2
unnamed: IC1.11 (D-), R30.2
unnamed: C131.1, IC1.9 (V_C_C_(_I_/O_)), JP1.2 (C)
unnamed: JTAG_LED1.1 (K), R66.1
unnamed: PWR_LED1.1 (K), R76.1
unnamed: R1.2, R2.2, U1.N18 (VDD_SB)
unnamed: R3.2, R4.2, U1.T18 (VDD_SB)
unnamed: R6.2, U1.U16 (GND)
unnamed: R10.2, U1.V16 (GND)
unnamed: R47.2, SWD1.1
unnamed: R48.2, SWD1.3
unnamed: R77.2, VDD_CORE_SET1.1
unnamed: R79.1, VDD_CORE_SET1.3
unnamed: R22.1, U1.V12 (SER_RTERM)
unnamed: R9.2, U1.N16 (NC)
unnamed: C82.1, R11.1, R12.1, U1.V15 (POR_ADJ)
unnamed: R54.1, U7.6 (SCLK)
unnamed: R58.1, U9.6 (SCLK)
unnamed: C111.1, Q1.2, U10.20 (XIN)
unnamed: R59.2, U10.21 (XOUT)
unnamed: R60.1, R64.1, U11.5 (FB)
unnamed: L3.1, U11.2 (SW)
unnamed: R61.1, R65.1, U12.5 (FB)
unnamed: L4.1, U12.2 (SW)
unnamed: R67.1, R71.1, U13.5 (FB)
unnamed: L5.1, U13.2 (SW)
unnamed: R68.1, R72.1, U14.5 (FB)
unnamed: L6.1, U14.2 (SW)
unnamed: R73.1, R78.1, U15.5 (FB), VDD_CORE_SET1.2
unnamed: L7.1, U15.2 (SW)
unnamed: R75.2, USB-C1.A5 (CC1)
unnamed: R74.2, USB-C1.B5 (CC2)
unnamed: R81.2, USB-C2.A5 (CC1)
unnamed: R80.2, USB-C2.B5 (CC2)
VDD_CORE: C30.1, C42.1, C46.1, C50.2, C51.2, C52.2, C53.2, C54.2, C55.2, C56.2, C57.2, C58.2, C59.2, C60.2, C61.2, C62.2, C63.2, C64.2, C65.2, C66.2, C67.2, C69.2, C71.2, C73.2, C75.2, C77.2, C125.1, C126.2, L1.1, L2.1, L7.2, R5.1, R73.2, U1.F9 (VDD), U1.G6 (VDD), U1.G8 (VDD), U1.G10 (VDD), U1.G12 (VDD), U1.H7 (VDD), U1.H9 (VDD), U1.H11 (VDD), U1.H13 (VDD), U1.J6 (VDD), U1.J8 (VDD), U1.J10 (VDD), U1.J12 (VDD), U1.K7 (VDD), U1.K9 (VDD), U1.K11 (VDD), U1.K13 (VDD), U1.L6 (VDD), U1.L8 (VDD), U1.L10 (VDD), U1.L12 (VDD), U1.M7 (VDD), U1.M9 (VDD), U1.M11 (VDD), U1.M13 (VDD), U1.N6 (VDD), U1.N8 (VDD), U1.N10 (VDD), VDD_CORE1.1 (Pad_1), VDD_CORE_E1.1, VDD_CORE_E1.2
VDD_EB: BANK_EB1.1, C2.1, C10.1, C18.2, C26.2, C34.2, U1.A16 (VDD_EB), U1.B18 (VDD_EB), U1.E14 (VDD_EB), U1.E17 (VDD_EB), U1.F13 (VDD_EB), VDD_EB_SEL1.2, VDD_EB_SEL1.4, VDD_EB_SEL1.6
VDD_NA: BANK_NA1.1, C7.2, C15.1, C23.1, C31.1, U1.A5 (VDD_NA), U1.B7 (VDD_NA), U1.E6 (VDD_NA), U1.E8 (VDD_NA), U1.F7 (VDD_NA), VDD_NA_SEL1.2, VDD_NA_SEL1.4, VDD_NA_SEL1.6
VDD_NB: BANK_NB1.1, C8.1, C16.2, C24.2, C32.2, U1.B10 (VDD_NB), U1.B13 (VDD_NB), U1.E10 (VDD_NB), U1.E12 (VDD_NB), U1.F11 (VDD_NB), VDD_NB_SEL1.2, VDD_NB_SEL1.4, VDD_NB_SEL1.6

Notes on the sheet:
Vout=0.6*(1+Ra/Rb)
USB Diff. Pair Zdiff=90 Ohms!
1-2 Closed
.55V
up to 250
/SER_TX_P2 in A4!
QSPI pins of RP2040 should be wired directly to the flash, using short connections
Note!: Take in mind that SerDes is not working when VDD_CORE = 0.9V (Low power mode), because VDDSER and VDDSER_PLL have got minimum working voltage: 0.95V!
Both Opened
Free Bank
Raspberry Pi Debug Probe has got 3.3V I/O Levels!
Close to RPi!
1.10V (Speed mode)
/SER_TX_P3 in A4!
Note! I/O Level = 2.5V!
Unequal Pins A1/A2/A4
0.9V
or VDA2710NTA
2V5 Levels
500~1000
/SER_TX_N3 in A4!
Power-Good Reset.
up to 416.75
1000~2000
ISO/IEC 7816 Interface
================ Unequal Pins A1/A2/A4! ================ Ball N18 is SER_RTERM3 in A4! Ball T18 is SER_RTERM2 in A4!
================ Unequal Pins A1/A2/A4! ================ Ball V15 is SER_RTERM1 in A2/A4!
1.0V
Cologne Chip GateMate FPGA - CCGM1A1(20,480 CPEs), CCGM1A2(40,960 CPEs) or CCGM1A4(81,920 CPEs)
OFF
Selectable VDD 1.2V/1.8V/2.5V/ User PWR_Supply
up to 312.5
Power-On Sequence: VDD_CORE -> +2V5 -> +3V3 -> +1V8 -> +1V2
POR_ADJ - Optional Components! Power-on-Reset level adjustment.
fDCO (MHz)
1.00V (Economy mode)
Tdelay(2.7V)=370ms
FPGA Oscillator
FPGA Button&LED
Clock rate: 100MHz(max) for fast read
